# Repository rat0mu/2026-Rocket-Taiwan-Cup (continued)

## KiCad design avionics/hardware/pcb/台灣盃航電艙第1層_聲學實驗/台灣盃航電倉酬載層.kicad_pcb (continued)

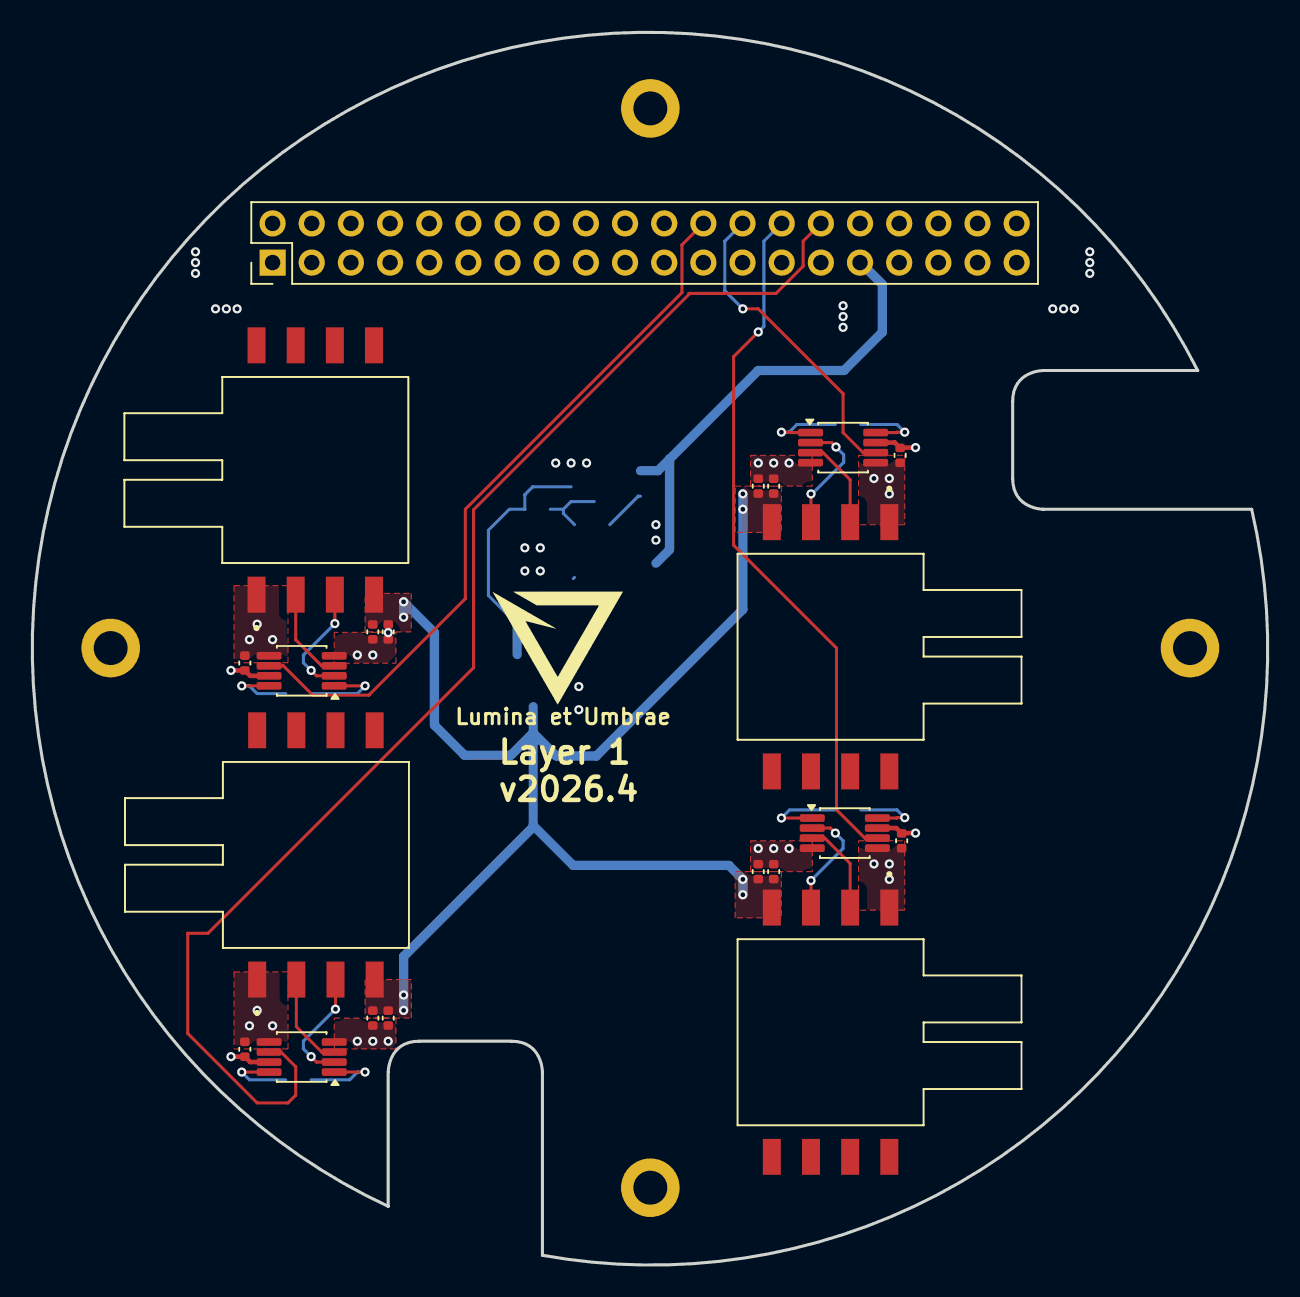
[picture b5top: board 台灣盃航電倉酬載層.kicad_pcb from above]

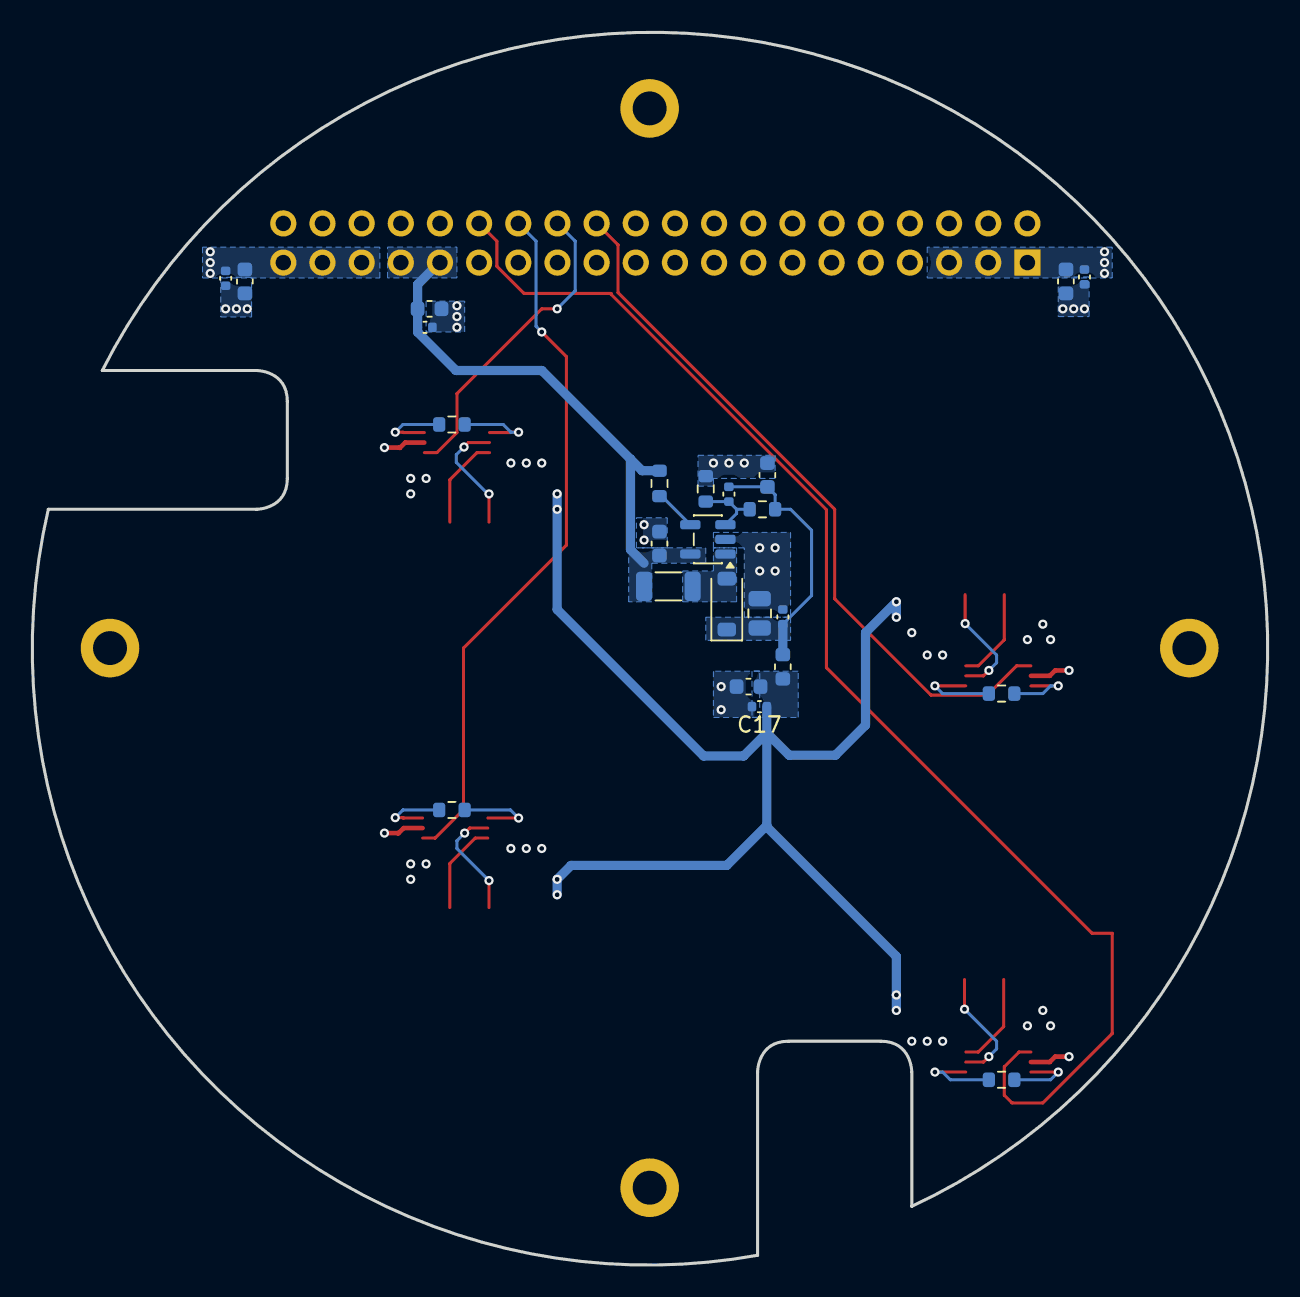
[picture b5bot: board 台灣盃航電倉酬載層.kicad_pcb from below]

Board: 4 copper layers, 80.1 x 79.9 mm, 49 parts (24 on the bottom side), 28 nets.

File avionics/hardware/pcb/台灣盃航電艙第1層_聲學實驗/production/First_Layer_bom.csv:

Designator,Footprint,Quantity,Value,LCSC Part #
C1,0603,1,2.2u,
C10,0402,1,220p,
C11,0603,1,4.7u,
"C12, C14, C16, C17, C19, C2, C20, C22, C23, C25",0402,10,0.1u,
C13,0805,1,22u,
"C15, C7, C8, C9",0603,4,10u,
"C18, C21, C24, C6",0402,4,1u,
"C3, C4, C5",0402,3,100n,
D1,D_SOD-123,1,MBR0520,
FB1,0603,1,FerriteBead,
L1,1206,1,10u,
"R1, R5, R6, R7",0603,4,2k,
R2,0603,1,51K,
R3,0603,1,24.9K,
R4,0603,1,178K,
"U1, U4, U7, U9",XDCR_MPXV2202DPT1,4,MPXV2202DPT1,
"U10, U2, U6, U8",VSSOP-8_3x3mm_P0.65mm,4,INA333xxDGK,
U3,SOT-23-5,1,LM2733YMF,
U5,PinHeader_2x20_P2.54mm_Vertical,1,Connector,

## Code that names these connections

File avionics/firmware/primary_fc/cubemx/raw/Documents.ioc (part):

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Mcu.Name=STM32F405VGTx
Mcu.Package=LQFP100
Mcu.UserName=STM32F405VGTx
PA0-WKUP.GPIOParameters=GPIO_Label
PA0-WKUP.GPIO_Label=GPS_RX
PA0-WKUP.Mode=Asynchronous
PA0-WKUP.Signal=UART4_TX
PA1.GPIOParameters=GPIO_Label
PA1.GPIO_Label=GPS_TX
PA1.Mode=Asynchronous
PA1.Signal=UART4_RX
PA10.GPIOParameters=GPIO_Label
PA10.GPIO_Label=LORA_TX
PA10.Mode=Asynchronous
PA10.Signal=USART1_RX
PA11.GPIOParameters=GPIO_Label
PA11.GPIO_Label=GPS_RESET
PA11.Signal=GPIO_Output
PA12.GPIOParameters=GPIO_Label
PA12.GPIO_Label=INT_GPS
PA12.Signal=GPXTI12
PA13.Mode=Serial_Wire
PA13.Signal=SYS_JTMS-SWDIO
PA14.Mode=Serial_Wire
PA14.Signal=SYS_JTCK-SWCLK
PA2.GPIOParameters=GPIO_Label
PA2.GPIO_Label=BACKUP_RX
PA2.Mode=Asynchronous
PA2.Signal=USART2_TX
PA3.GPIOParameters=GPIO_Label
PA3.GPIO_Label=CS_IMU_GYRO
PA3.Signal=GPIO_Output
PA4.GPIOParameters=GPIO_Label
PA4.GPIO_Label=CS_IMU_ACCEL
PA4.Signal=GPIO_Output
PA5.Mode=Full_Duplex_Master
PA5.Signal=SPI1_SCK
PA6.Mode=Full_Duplex_Master
PA6.Signal=SPI1_MISO
PA7.Mode=Full_Duplex_Master
PA7.Signal=SPI1_MOSI
PA9.GPIOParameters=GPIO_Label
PA9.GPIO_Label=LORA_RX
PA9.Mode=Asynchronous
PA9.Signal=USART1_TX
PB0.GPIOParameters=GPIO_Label
PB0.GPIO_Label=PAYLOAD_1
PB0.Signal=ADCx_IN8
PB1.GPIOParameters=GPIO_Label
PB1.GPIO_Label=PAYLOAD_2
PB1.Signal=ADCx_IN9
PB10.Mode=Full_Duplex_Master
PB10.Signal=SPI2_SCK
PB14.GPIOParameters=GPIO_Label
PB14.GPIO_Label=INT_BARO
PB14.Signal=GPXTI14
PB15.GPIOParameters=GPIO_Label
PB15.GPIO_Label=INT_MAG
PB15.Signal=GPXTI15
PB4.GPIOParameters=GPIO_Label
PB4.GPIO_Label=LORA_AUX
PB4.Signal=GPXTI4
PB5.GPIOParameters=GPIO_Label
PB5.GPIO_Label=LORA_M0
PB5.Signal=GPIO_Output
PB6.GPIOParameters=GPIO_Label
PB6.GPIO_Label=LORA_M1
PB6.Signal=GPIO_Output
PB7.GPIOParameters=GPIO_Label
PB7.GPIO_Label=LORA_RESET
PB7.Signal=GPIO_Output
PC0.GPIOParameters=GPIO_Label
PC0.GPIO_Label=PAYLOAD_3
PC0.Signal=ADCx_IN10
PC1.GPIOParameters=GPIO_Label
PC1.GPIO_Label=PAYLOAD_4
PC1.Signal=ADCx_IN11
PC10.Mode=SD_4_bits_Wide_bus
PC10.Signal=SDIO_D2
PC11.Mode=SD_4_bits_Wide_bus
PC11.Signal=SDIO_D3
PC12.Mode=SD_4_bits_Wide_bus
PC12.Signal=SDIO_CK
PC2.Mode=Full_Duplex_Master
PC2.Signal=SPI2_MISO
PC3.Mode=Full_Duplex_Master
PC3.Signal=SPI2_MOSI
PC5.GPIOParameters=GPIO_Label
PC5.GPIO_Label=INT3_IMU_GYRO
PC5.Signal=GPXTI5
PC8.Mode=SD_4_bits_Wide_bus
PC8.Signal=SDIO_D0
PC9.Mode=SD_4_bits_Wide_bus
PC9.Signal=SDIO_D1
PD1.GPIOParameters=GPIO_Label
PD1.GPIO_Label=SDIO_DET
PD1.Signal=GPIO_Output
PD2.Mode=SD_4_bits_Wide_bus
PD2.Signal=SDIO_CMD
PD6.GPIOParameters=GPIO_Label
PD6.GPIO_Label=BACKUP_TX
PD6.Mode=Asynchronous
PD6.Signal=USART2_RX
PD8.GPIOParameters=GPIO_Label
PD8.GPIO_Label=DRDY_MAG
PD8.Signal=GPXTI8
PE13.GPIOParameters=GPIO_Label
PE13.GPIO_Label=CS_MAG
PE13.Signal=GPIO_Output
PE14.GPIOParameters=GPIO_Label
PE14.GPIO_Label=CS_BARO
PE14.Signal=GPIO_Output
PE15.GPIOParameters=GPIO_Label
PE15.GPIO_Label=CS_ACCEL
PE15.Signal=GPIO_Output
PE2.GPIOParameters=GPIO_Label
PE2.GPIO_Label=PYRO1
PE2.Signal=GPIO_Output
PE3.GPIOParameters=GPIO_Label
PE3.GPIO_Label=PYRO2
PE3.Signal=GPIO_Output
PE9.GPIOParameters=GPIO_Label
PE9.GPIO_Label=GPS_PPS
PE9.Signal=S_TIM1_CH1
PH0-OSC_IN.Mode=HSE-External-Oscillator
PH0-OSC_IN.Signal=RCC_OSC_IN
PH1-OSC_OUT.Mode=HSE-External-Oscillator
PH1-OSC_OUT.Signal=RCC_OSC_OUT
RCC.HSE_VALUE=16000000
RCC.SYSCLKFreq_VALUE=168000000
RCC.SYSCLKSource=RCC_SYSCLKSOURCE_PLLCLK
board=custom

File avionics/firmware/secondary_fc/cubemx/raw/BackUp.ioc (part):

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Mcu.Name=STM32F103C(8-B)Tx
Mcu.Package=LQFP48
Mcu.UserName=STM32F103C8Tx
PA0-WKUP.GPIOParameters=GPIO_Label
PA0-WKUP.GPIO_Label=INT_GPS
PA0-WKUP.Signal=GPXTI0
PA1.GPIOParameters=GPIO_Label
PA1.GPIO_Label=INT_BARO
PA1.Signal=GPXTI1
PA10.Mode=Asynchronous
PA10.Signal=USART1_RX
PA11.GPIOParameters=GPIO_Label
PA11.GPIO_Label=CS_IMU_GYRO
PA11.Signal=GPIO_Output
PA12.GPIOParameters=GPIO_Label
PA12.GPIO_Label=CS_IMU_ACCEL
PA12.Signal=GPIO_Output
PA13.Mode=Serial_Wire
PA13.Signal=SYS_JTMS-SWDIO
PA14.Mode=Serial_Wire
PA14.Signal=SYS_JTCK-SWCLK
PA15.GPIOParameters=GPIO_Label
PA15.GPIO_Label=CS_BARO
PA15.Signal=GPIO_Output
PA2.Mode=Asynchronous
PA2.Signal=USART2_TX
PA3.Mode=Asynchronous
PA3.Signal=USART2_RX
PA5.Mode=Full_Duplex_Master
PA5.Signal=SPI1_SCK
PA6.Mode=Full_Duplex_Master
PA6.Signal=SPI1_MISO
PA7.Mode=Full_Duplex_Master
PA7.Signal=SPI1_MOSI
PA9.Mode=Asynchronous
PA9.Signal=USART1_TX
PB1.GPIOParameters=GPIO_Label
PB1.GPIO_Label=PYRO_1
PB1.Signal=GPIO_Output
PB10.Mode=Asynchronous
PB10.Signal=USART3_TX
PB11.Mode=Asynchronous
PB11.Signal=USART3_RX
PB13.Mode=Full_Duplex_Master
PB13.Signal=SPI2_SCK
PB14.Mode=Full_Duplex_Master
PB14.Signal=SPI2_MISO
PB15.Mode=Full_Duplex_Master
PB15.Signal=SPI2_MOSI
PB2.GPIOParameters=GPIO_Label
PB2.GPIO_Label=PYRO_2
PB2.Signal=GPIO_Output
PB3.GPIOParameters=GPIO_Label
PB3.GPIO_Label=GPS_PPS
PB3.Signal=S_TIM2_CH2
PB4.GPIOParameters=GPIO_Label
PB4.GPIO_Label=CS_SD
PB4.Signal=GPIO_Output
PB5.GPIOParameters=GPIO_Label
PB5.GPIO_Label=LORA_AUX
PB5.Signal=GPXTI5
PB6.GPIOParameters=GPIO_Label
PB6.GPIO_Label=LORA_RESET
PB6.Signal=GPIO_Output
PB7.GPIOParameters=GPIO_Label
PB7.GPIO_Label=GPS_RESET
PB7.Signal=GPIO_Output
PB8.GPIOParameters=GPIO_Label
PB8.GPIO_Label=LORA_M0
PB8.Signal=GPIO_Output
PB9.GPIOParameters=GPIO_Label
PB9.GPIO_Label=LORA_M1
PB9.Signal=GPIO_Output
PC13-TAMPER-RTC.GPIOParameters=GPIO_Label
PC13-TAMPER-RTC.GPIO_Label=INT1_IMU_ACCEL
PC13-TAMPER-RTC.Signal=GPXTI13
PC14-OSC32_IN.GPIOParameters=GPIO_Label
PC14-OSC32_IN.GPIO_Label=INT3_IMU_GYRO
PC14-OSC32_IN.Signal=GPXTI14
PD0-OSC_IN.Mode=HSE-External-Oscillator
PD0-OSC_IN.Signal=RCC_OSC_IN
PD1-OSC_OUT.Mode=HSE-External-Oscillator
PD1-OSC_OUT.Signal=RCC_OSC_OUT
RCC.SYSCLKFreq_VALUE=72000000
RCC.SYSCLKSource=RCC_SYSCLKSOURCE_PLLCLK
board=custom

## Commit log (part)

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2026-04-17 Initial project structure
2026-04-17 Add PCB design files
2026-04-17 Reorganize repository structure and add bilingual README
2026-04-17 Reorganize repository into system-level architecture
2026-04-17 Rename mechanical subsystem to structure
2026-04-17 Track empty subsystem directories with gitkeep
2026-04-18 Adding AGENTS.MD file
2026-04-19 更新下層PCB原理圖
2026-04-19 Delete avionics/hardware/pcb/台灣盃航電倉下層 directory
    This version has been replaced by version 1.0.
2026-04-19 Add files via upload
    this is the version 1.0
2026-04-19 對上層PCB的布局進行了一些修改
2026-04-20 Add files via upload
    This is V1.1
    add via stitch to increase heat dissipation capacity
    change layer from 4 to 2, and increase thickness to 0.07mm
    resolve the DRC problem
    change the pad connection of the connector
2026-04-20 完成上層PCB
2026-04-21 更新酬載層內容
2026-04-21 V1.2
    change Schottky Diode to nmos
    change the footprint of the 1n5824*2
    change the circuit of the LM2596S-5*2
    change the position of the igition*2
2026-04-22 V1.0板
    更新原理圖
    layout 完PCB，並且沒有任何DRC錯誤及警告
    增加三個感測器的封裝上去
2026-04-27 完成所有航電板設計
2026-04-28 更改航電PCB檔名
2026-04-28 上傳新的連接器
2026-04-28 將第一至三層連接器修改成PC104規格，第四層還未進行
2026-04-28 刪除Propulsion資料夾
2026-04-29 Add files via upload
    change schematics
2026-04-29 更新第4,5層PCB
2026-04-30 更新PCB圖，記得要直接下載PCB檔
2026-05-03 完成PCB最終設計
2026-05-14 航電倉第二層
2026-05-14 航電倉第一層
2026-05-14 航電倉第三層
2026-05-14 航電倉第四層
2026-05-14 航電倉第五層
2026-05-14 剩餘的零組件及支架模型
